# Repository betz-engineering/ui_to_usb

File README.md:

# ui_to_usb
Interface board to attach `ui_board_1u` to a PC or embedded computer over USB.
Based on a CH32V203 chip to handle the SPI interface and reading the encoder.

  * [Schematic](pics/ui_to_usb.pdf)
  * [Firmware](https://github.com/betz-engineering/ui_to_usb_firmware)

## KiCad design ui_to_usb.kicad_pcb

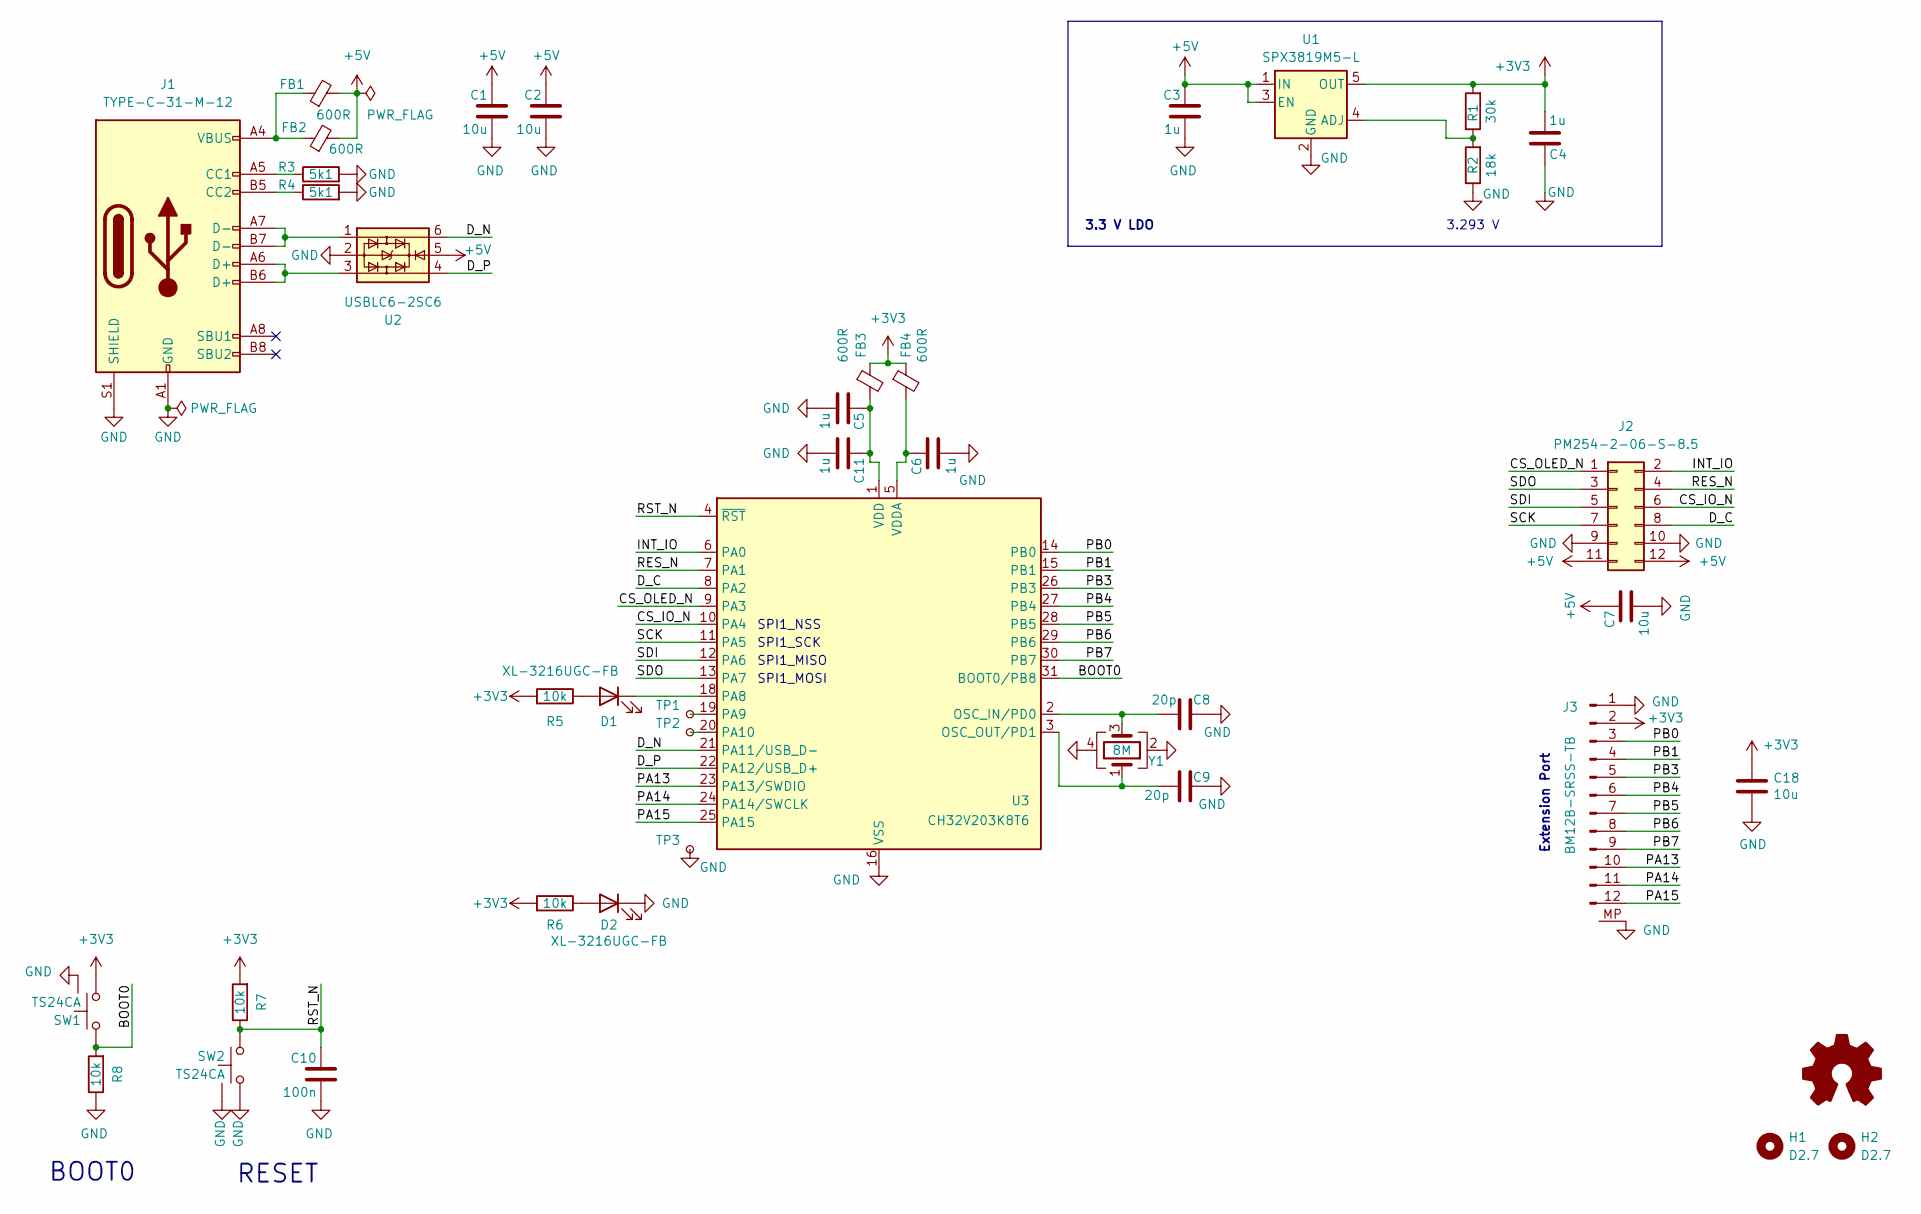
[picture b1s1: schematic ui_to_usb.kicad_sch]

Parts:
C1, C2, C7, C18: 10u; C_1206_3216Metric
C3, C4, C5, C6, C11: 1u; C_0603_1608Metric
C8, C9: 20p; C_0603_1608Metric
C10: 100n; C_0603_1608Metric
D1, D2: XL-3216UGC-FB; LED_1206_3216Metric_ReverseMount_Hole2.0x1.6mm
FB1, FB2, FB3, FB4: 600R; L_0603_1608Metric; JLCPCB Part # C19330
H1, H2: D2.7; MountingHole_2.7mm_M2.5_ISO7380_Pad
J1: TYPE-C-31-M-12; USB_C_Receptacle_GCT_USB4105-xx-A_16P_TopMnt_Horizontal
J2: PM254-2-06-S-8.5; PinSocket_2x06_P2.54mm_Vertical_SMD
J3: BM12B-SRSS-TB; JST_SH_BM12B-SRSS-TB_1x12-1MP_P1.00mm_Vertical; LCSC Part # C160393
R1: 30k; R_0603_1608Metric
R2: 18k; R_0603_1608Metric
R3, R4: 5k1; R_0603_1608Metric
R5, R6, R7, R8: 10k; R_0603_1608Metric
SW1, SW2: TS24CA
TP1: A9; TestPoint_Pad_D1.0mm
TP2: A10; TestPoint_Pad_D1.0mm
TP3: GND; TestPoint_Pad_D1.0mm
U1: SPX3819M5-L; SOT-23-5; LCSC Part # C9056
U2: USBLC6-2SC6; SOT-23-6
U3: CH32V203K8T6; LQFP-32_7x7mm_P0.8mm
Y1: 8M; Crystal_SMD_3225-4Pin_3.2x2.5mm; JLCPCB Part # C2682774

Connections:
+3V3: C4.1, C18.1, FB3.1, FB4.1, J3.2, R1.2, R5.2, R6.2, R7.2, SW1.1, U1.5 (OUT)
+5V: C1.2, C2.2, C3.2, C7.2, FB1.2, FB2.2, J2.11, J2.12, U1.1 (IN), U1.3 (EN), U2.5
/BOOT0: R8.2, SW1.2, U3.31 (BOOT0/PB8)
/CS_IO_N: J2.6, U3.10 (PA4)
/CS_OLED_N: J2.1, U3.9 (PA3)
/D_C: J2.8, U3.8 (PA2)
/D_N: U2.6, U3.21 (PA11/USB_D-)
/D_P: U2.4, U3.22 (PA12/USB_D+)
/INT_IO: J2.2, U3.6 (PA0)
/PA13: J3.10, U3.23 (PA13/SWDIO)
/PA14: J3.11, U3.24 (PA14/SWCLK)
/PA15: J3.12, U3.25 (PA15)
/PB0: J3.3, U3.14 (PB0)
/PB1: J3.4, U3.15 (PB1)
/PB3: J3.5, U3.26 (PB3)
/PB4: J3.6, U3.27 (PB4)
/PB5: J3.7, U3.28 (PB5)
/PB6: J3.8, U3.29 (PB6)
/PB7: J3.9, U3.30 (PB7)
/RES_N: J2.4, U3.7 (PA1)
/RST_N: C10.2, R7.1, SW2.2, U3.4 (~RST)
/SCK: J2.7, U3.11 (PA5)
/SDI: J2.5, U3.12 (PA6)
/SDO: J2.3, U3.13 (PA7)
GND: C1.1, C2.1, C3.1, C4.2, C5.1, C6.1, C7.1, C8.1, C9.1, C10.1, C11.1, C18.2, D2.1 (K), J1.A1 (GND), J1.A12 (GND), J1.B1 (GND), J1.B12 (GND), J1.S1 (SHIELD), J2.9, J2.10, J3.1, J3.MP, R2.1, R3.2, R4.2, R8.1, SW1.0, SW2.0, SW2.1, TP3.1, U1.2 (GND), U2.2, U3.16 (VSS), U3.32 (VSS), Y1.2, Y1.4
unnamed: D1.2 (A), R5.1
unnamed: D1.1 (K), U3.18 (PA8)
unnamed: D2.2 (A), R6.1
unnamed: FB1.1, FB2.1, J1.A4 (VBUS), J1.A9 (VBUS), J1.B4 (VBUS), J1.B9 (VBUS)
unnamed: J1.A5 (CC1), R3.1
unnamed: J1.B5 (CC2), R4.1
unnamed: J1.A6 (D+), J1.B6 (D+), U2.3
unnamed: J1.A7 (D-), J1.B7 (D-), U2.1
unnamed: R1.1, R2.2, U1.4 (ADJ)
unnamed: C8.2, U3.2 (OSC_IN/PD0), Y1.3
unnamed: C9.2, U3.3 (OSC_OUT/PD1), Y1.1
unnamed: TP1.1, U3.19 (PA9)
unnamed: TP2.1, U3.20 (PA10)
unnamed: C6.2, FB4.2, U3.5 (VDDA)
VDD: C5.2, C11.2, FB3.2, U3.1 (VDD), U3.17 (VDD)

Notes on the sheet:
SPI1_MISO
SPI1_SCK
3.293 V
Extension Port
RESET
BOOT0
SPI1_MOSI
SPI1_NSS
3.3 V LDO

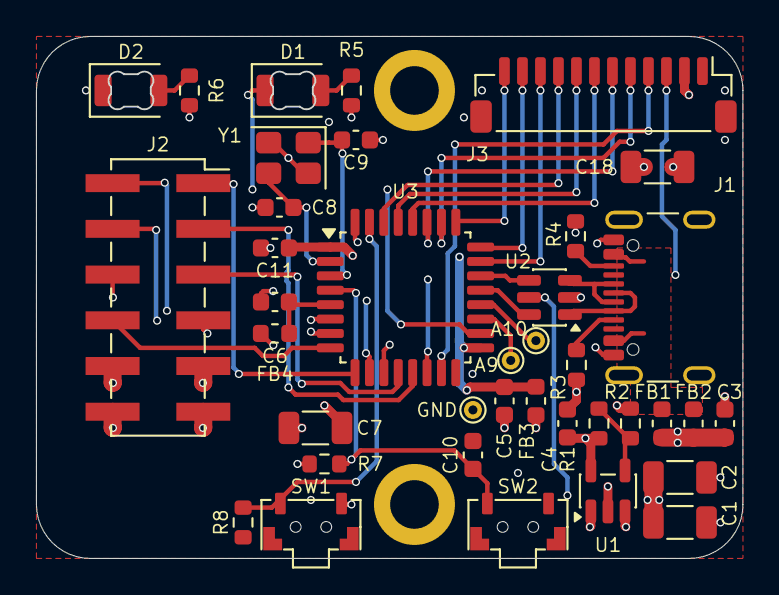
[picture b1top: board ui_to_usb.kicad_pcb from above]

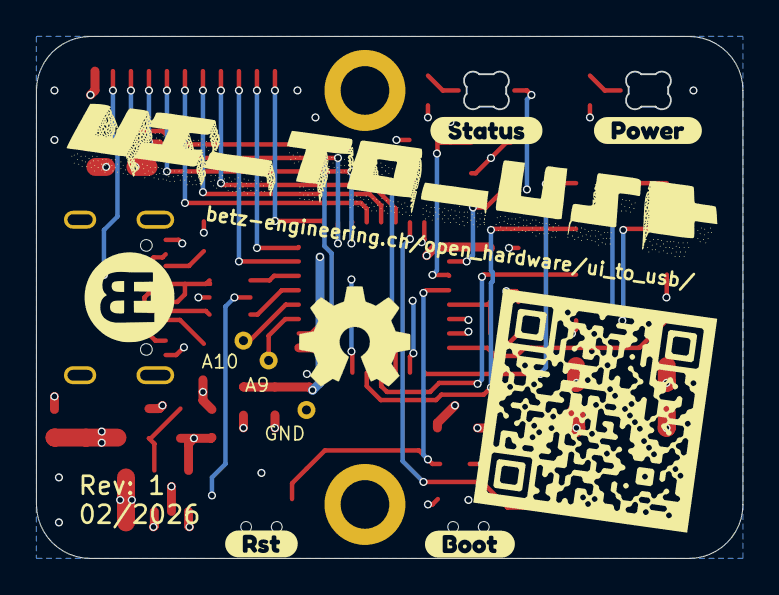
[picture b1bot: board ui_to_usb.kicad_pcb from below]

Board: 4 copper layers, 39.2 x 29.0 mm, 46 parts (6 on the bottom side), 40 nets.

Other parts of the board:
G1: LOGO
G2: OSHW-Logo2_9.8x8mm_SilkScreen
kibuzzard-698F164A: G***; kibuzzard-698F164A
kibuzzard-698F1642: G***; kibuzzard-698F1642
kibuzzard-6951C42C: G***; kibuzzard-6951C42C
kibuzzard-6951C425: G***; kibuzzard-6951C425

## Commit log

2025-12-28 initial commit
    * layout mostly completed
    * no DRC done yet
2025-12-28 add silkscreen
    fix all DRC errors
2025-12-29 move flash chip out of the way
2025-12-29 bigger cut-out for LEDs. Add README and renders
2026-01-09 check sch and pcb before production, looks ready
2026-01-09 improve BOM, ordered rev -
2026-01-16 add ft232h.conf file
    * contains the serial of the last programmed device
2026-01-26 add CH32V305G (QFN28) symbol
2026-01-29 schematic progress
2026-01-31 switch to CH32V203
    as the V305 I've selected before doesn't have a BOOT0 pin
2026-01-31 schematic updates
2026-02-01 add extension port
2026-02-02 explore placement
2026-02-04 switch to 4 layers, all traces routed
2026-02-04 add tactile button footprint
2026-02-05 layout looks decent, 0 DRC errors
2026-02-12 Layout looks decent. Ready to order.
2026-02-13 moved tactile buttons because of colission with shroud on ui_board_1u
2026-02-13 change 3V3 feedback resistor for more common values
    sent for production
